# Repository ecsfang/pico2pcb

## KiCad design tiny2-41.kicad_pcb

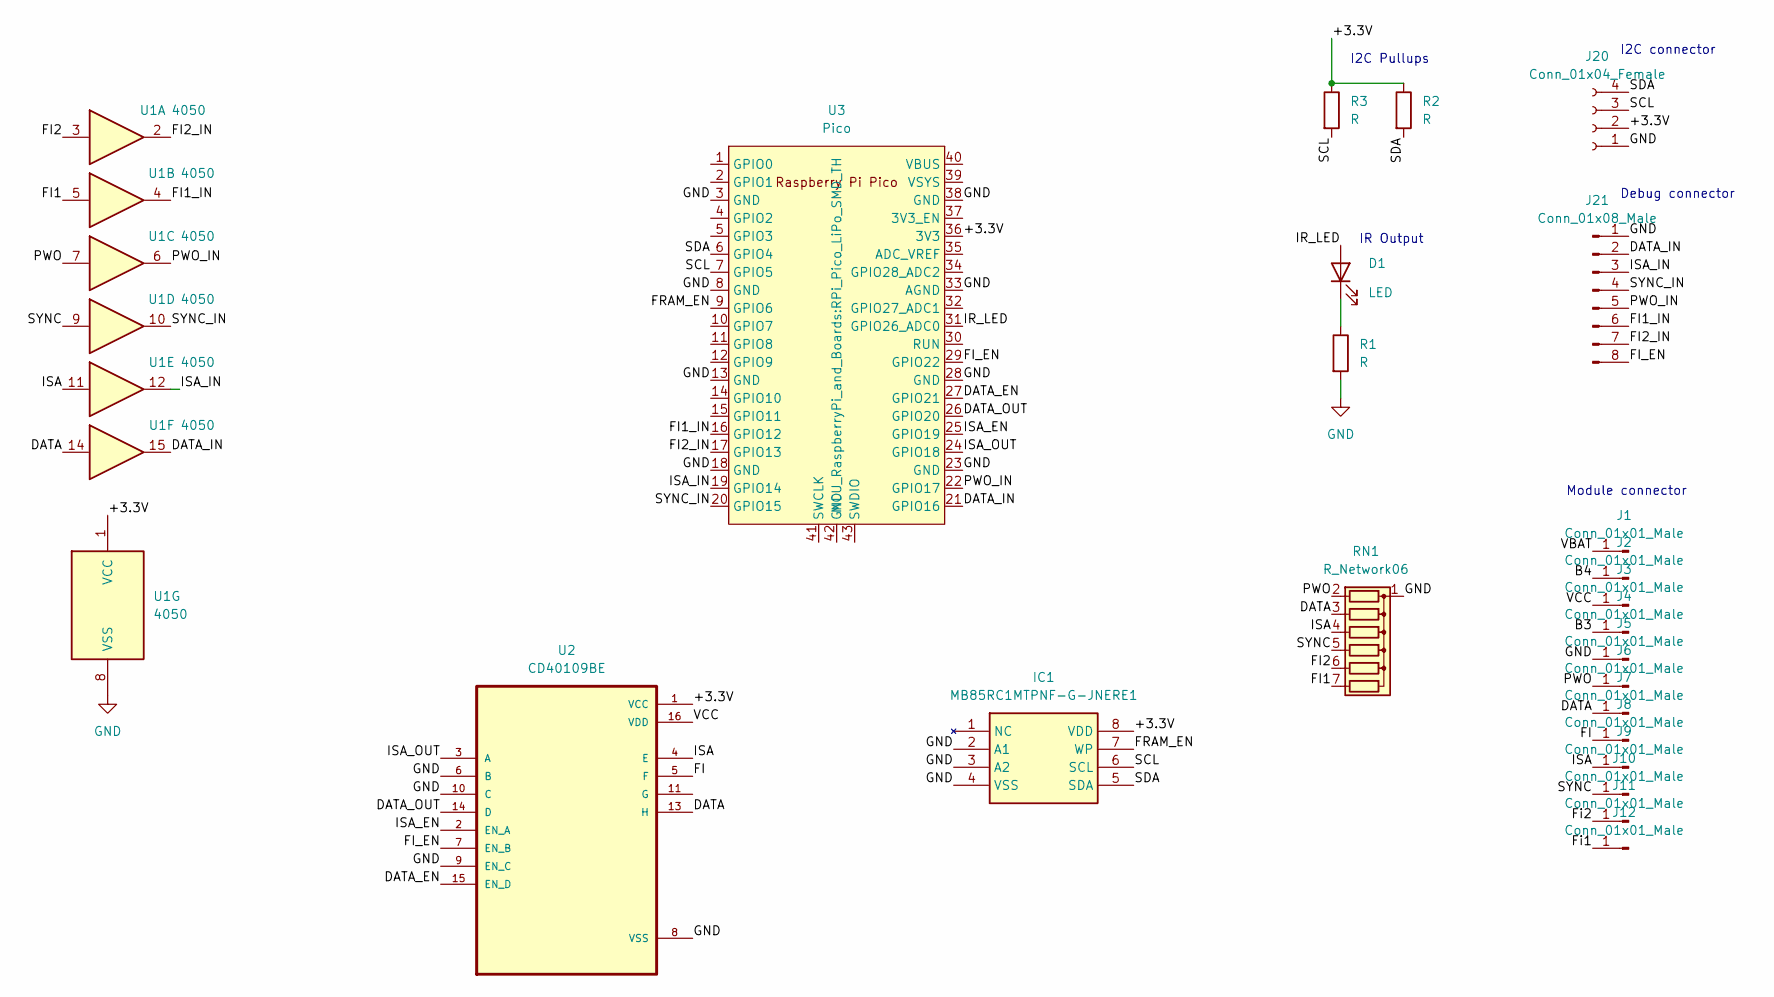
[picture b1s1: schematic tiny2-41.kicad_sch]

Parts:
D1: LED; LED_D3.0mm
IC1: MB85RC1MTPNF-G-JNERE1; SOIC127P600X175-8N; Mouser Part Number 249-85C1MTPNFGJNERE1
J1, J2, J3, J4, J5, J6, J7, J8, J9, J10, J11, J12: Conn_01x01_Male; TestPoint_Pad_1.0x1.0mm
J20: Conn_01x04_Female; PinHeader_1x04_P2.54mm_Vertical
J21: Conn_01x08_Male; PinSocket_1x08_P2.54mm_Vertical
R1, R2, R3: R; R_Axial_DIN0207_L6.3mm_D2.5mm_P7.62mm_Horizontal
RN1: R_Network06; 4607X101105LF
U1: 4050; SO16
U2: CD40109BE; SO16
U3: Pico; RPi_Pico_LiPo_SMD_TH

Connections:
/+3.3V: IC1.8 (VDD), J20.2, R2.1, R3.1, U1.1 (VCC), U2.1 (VCC), U3.36 (3V3)
/B3: J4.1
/B4: J2.1
/DATA: J7.1, RN1.3 (R2), U1.14, U2.13 (H)
/DATA_EN: U2.15 (EN_D), U3.27 (GPIO21)
/DATA_IN: J21.2, U1.15, U3.21 (GPIO16)
/DATA_OUT: U2.14 (D), U3.26 (GPIO20)
/FI: J8.1, U2.5 (F)
/FI1: RN1.7 (R6), U1.5
/FI1_IN: J21.6, U1.4, U3.16 (GPIO12)
/FI2: RN1.6 (R5), U1.3
/FI2_IN: J21.7, U1.2, U3.17 (GPIO13)
/FI_EN: J21.8, U2.7 (EN_B), U3.29 (GPIO22)
/FRAM_EN: IC1.7 (WP), U3.9 (GPIO6)
/Fi1: J12.1
/Fi2: J11.1
/IR_LED: D1.2 (A), U3.31 (GPIO26_ADC0)
/ISA: J9.1, RN1.4 (R3), U1.11, U2.4 (E)
/ISA_EN: U2.2 (EN_A), U3.25 (GPIO19)
/ISA_IN: J21.3, U1.12, U3.19 (GPIO14)
/ISA_OUT: U2.3 (A), U3.24 (GPIO18)
/PWO: J6.1, RN1.2 (R1), U1.7
/PWO_IN: J21.5, U1.6, U3.22 (GPIO17)
/SCL: IC1.6 (SCL), J20.3, R3.2, U3.7 (GPIO5)
/SDA: IC1.5 (SDA), J20.4, R2.2, U3.6 (GPIO4)
/SYNC: J10.1, RN1.5 (R4), U1.9
/SYNC_IN: J21.4, U1.10, U3.20 (GPIO15)
/VBAT: J1.1
/VCC: J3.1, U2.16 (VDD)
GND: IC1.2 (A1), IC1.3 (A2), IC1.4 (VSS), J5.1, J20.1, J21.1, R1.2, RN1.1 (common), U1.8 (VSS), U2.6 (B), U2.8 (VSS), U2.9 (EN_C), U2.10 (C), U3.3 (GND), U3.8 (GND), U3.13 (GND), U3.18 (GND), U3.23 (GND), U3.28 (GND), U3.33 (AGND), U3.38 (GND)
unnamed: D1.1 (K), R1.1

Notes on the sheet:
Debug connector
I2C connector
I2C Pullups
Module connector
IR Output

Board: 2 copper layers, 23 parts (0 on the bottom side), 26 nets, no tracks yet.

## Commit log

2024-09-10 Added FRAM
2024-09-11 Updated ...
